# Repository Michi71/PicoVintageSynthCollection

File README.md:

# PicoVintageSynthCollection

Thirteen vintage synthesizer emulations for the RP2350, built from one shared
codebase. Same board, same core, one firmware image per instrument.

<p align="center">
  
  <br>
  
  <br>
  <sub>Rendered on a host from the firmware's own drawing code
  (<a href="tools/host_tests/ui/README.md">tools/host_tests/ui</a>) &mdash; what the OLED shows, pixel for pixel.</sub>
</p>

## Demo

<p align="center">
  
  <br>
  <a href="https://youtu.be/6L494ZGSKgw">&#9654; PicoFaceM1 demo on YouTube</a> &mdash; the Korg M1 on the project's own PCB
  <br><br>
  <a href="https://youtu.be/cG6gyhaqCxE">&#9654; Earlier demo of the collection</a>
</p>

## Project philosophy and architecture

**Translation, not emulation.** No instrument here runs an emulated CPU or
system bus, as MAME-style emulators do. Each one is a native C++17 engine on a
shared core, and how it was derived depends on what the original leaves to
work with:

- The **Korg M1** and the **Roland D-50** come from a disassembly of the
  original operating system: envelopes, filters, voice allocation and the
  effect algorithms were read out of the firmware and rewritten as native
  code that plays the machine's own PCM data. Where firmware, plugin and ear
  disagree, the firmware wins.
- The **Roland CM-32L** is the one that runs somebody else's engine: the
  synthesis core of [munt](https://github.com/munt/munt)'s mt32emu, which
  models the LA32 chip and restates the module's firmware, with the original
  control and PCM ROM. It was reshaped to fit the board - both cores render,
  the code that plays runs from RAM - and still produces upstream's samples.
- The **JV-880** and the **RD/MKS-20** are written over the original PCM data
  and calibrated against a reference emulator of the original firmware, which
  runs on the host only and is not part of this repository.
- The analog and modern instruments are modeled from manuals, schematics and
  published work; the License section lists every upstream.

**Lean because it has to be.** Every engine has to finish its audio blocks on
an RP2350, a microcontroller with 520 KB of RAM, overclocked to 444 MHz. That
budget leaves no room for waste: tables live in flash, the voice loops are
measured on the device, and an instrument that does not fit does not ship.
The same engine sources also build unchanged on macOS for the host tests,
which is what makes them portable to other targets.

**Made for reuse.** The engines are separate from the core that drives the
hardware (display, encoders, MIDI, audio output). Taking an engine, a filter
or an effect into your own hardware, plugin or application is an explicit
goal, under the GPL-3 terms below.

**How it is made.** The project is developed with an AI coding agent
(Claude Code); the rules it works under are in [CLAUDE.md](CLAUDE.md). It
does not build itself. The author sets the goals, the order of authority and
the bar for "done", decides every trade-off, builds the hardware and tests
on it: no firmware change is merged without a hardware test. The agent does a large
share of the disassembly analysis and the code. Every result is checked
against the original firmware, a reference render or a measurement before it
lands, and what could not be verified is written down as such in the
instrument's documentation.

## Instruments

| Folder | Instrument | Binary |
|---|---|---|
| [instruments/PicoFaceYC](instruments/PicoFaceYC/README.md) | Yamaha reface YC (drawbar organ) | PicoFaceYC.uf2 |
| [instruments/PicoFaceCP](instruments/PicoFaceCP/README.md) | Yamaha reface CP (electric piano, mdaEPiano) | PicoFaceCP.uf2 |
| [instruments/PicoFaceDX](instruments/PicoFaceDX/README.md) | Yamaha reface DX (4-operator FM) | PicoFaceDX.uf2 |
| [instruments/PicoFaceJ6](instruments/PicoFaceJ6/README.md) | Roland Juno-6 | PicoFaceJ6.uf2 |
| [instruments/PicoFaceMD](instruments/PicoFaceMD/README.md) | Minimoog Model D | PicoFaceMD.uf2 |
| [instruments/PicoFaceSM](instruments/PicoFaceSM/README.md) | ARP/Eminent Solina String Ensemble | PicoFaceSM.uf2 |
| [instruments/PicoFaceOB](instruments/PicoFaceOB/README.md) | Oberheim OB-X (engine ported from OB-Xf) | PicoFaceOB.uf2 |
| [instruments/PicoFaceVS](instruments/PicoFaceVS/README.md) | Sequential Prophet VS (native vector-synthesis engine, with edit pages and SysEx) | PicoFaceVS.uf2 |
| [instruments/PicoFaceRD](instruments/PicoFaceRD/README.md) | Roland RD / MKS-20 (sample piano) | local build only |
| [instruments/PicoFaceJV](instruments/PicoFaceJV/README.md) | Roland JV-880 (native engine over the original PCM data) | local build only |
| [instruments/PicoFaceD5](instruments/PicoFaceD5/README.md) | Roland D-50 (native LA engine over the original PCM data) | local build only |
| [instruments/PicoFaceM1](instruments/PicoFaceM1/README.md) | Korg M1 (native engine over the original PCM data, with edit pages and SysEx) | local build only |
| [instruments/PicoFaceCM](instruments/PicoFaceCM/README.md) | Roland CM-32L (mt32emu's LA synthesis core over the original ROMs, eight parts and rhythm, on both cores) | local build only |

The RD, the JV-880, the D-50, the M1 and the CM-32L are the exceptions to "download and flash":
they only build where the respective ROM set is present, and those ROMs are not
distributable, so none of them is in the release binaries. Without them
the configure step skips them and the eight above are unaffected. All of them run
on the hardware; see the flash note below for the one build option the JV-880
needs on a small board.

## Hardware

- RP2350; the reference board carries 16 MB of flash, 4 MB is enough for every
  instrument but the JV-880 (see [How much flash an instrument needs](#how-much-flash-an-instrument-needs)).
  **The board must feed the core from the RP2350's own regulator** -- see
  *The board has to take the overclock* below before buying anything cheap.
- I2S audio (PCM5102 DAC)
- 128x64 OLED over I2C (SH1106)
- Three rotary encoders with push buttons
- USB MIDI and DIN MIDI

The pin map is the same for every instrument and lives in
[core/include/project_config.h](core/include/project_config.h).

**Which RP2350 board.** The default build assumes a Pico-2-format board with an
RP2350**A** -- Pico 2, Waveshare RP2350-Plus and the like -- where I2S sits on
GP26/27/28 at header pins 31/32/34. The Waveshare **RP2350B-Plus-W** has the
same header but carries **GP40/41/42** at those three positions (the RP2350B's
ADC0-2 take the Pico's ADC spots; GP26-28 are only on the pads underneath), so
a default image on it drives the I2S lines into thin air: display, MIDI and
encoders work, only the sound is missing, and every counter reads healthy. It
is a build-time choice, not a wiring one -- see *Building* for
`-DPICOFACE_BOARD=rp2350b_plus_w`.

**The board has to take the overclock.** These engines are budgeted for a
core clock of **444 MHz** (480 for the RD) at a core voltage of **1.60 V**:
three times the RP2350's rated 150 MHz, and a voltage above what the SDK
allows without an explicit override. That is not a tuning option, it is the
design point -- below it the instruments do not finish their audio blocks.
The firmware sets that voltage through the chip's on-board regulator, so the
board has to route the core supply (`DVDD`) through that regulator, the way
the Pico 2 reference design does. **Known good:** Raspberry Pi Pico 2,
Waveshare RP2350-Plus, Waveshare RP2350B-Plus-W (with its build variant).
**Known bad:** unbranded 16 MB "RP2350" boards from marketplace sellers. One
was bought to settle issue #107: its chip and flash are fine, but the
regulator register has no effect on its core voltage, so the core stays at the
board's fixed supply and stops dead at 312 MHz. No build option, flash timing
or stepping has anything to do with it, and no firmware can get 444 MHz from
such a board. The symptom is either nothing on the screen with the release
image, or "boots at 300 MHz, no sound" with a downclocked build. If a board
does neither of the things above, the working image is the diagnosis: build
`PicoFaceMD` with `-DPICOFACE_BOOT_DIAG=ON` and read the last line on the
screen; the whole investigation, with the images that separate flash, core
and voltage, is in the MD README under
[The board that stops at 300 MHz](instruments/PicoFaceMD/README.md#the-board-that-stops-at-300-mhz-a-core-voltage-the-register-cannot-reach).
Please check that section before opening an issue about a board that will
not start: a chip marked `A4` is not the reason either (the splash shows the
bootrom revision as `b4` now, and it changes nothing).

**If the screen stays dark.** The panel is on I2C at 1 MHz with only the chip's
internal pull-ups. That is above what an SH1106 datasheet promises (400 kHz) and
it is what the reference board runs, because the display push is paced in half
tile rows of roughly 1.5 ms of I2C each -- the bus rate is directly the UI's
frame time, and 400 kHz would make a full screen 60 ms instead of 24. On longer
jumper leads it is the first thing to suspect. Build with
`-DPICOFACE_OLED_I2C_HZ=400000`, and consider real 2.2k-4.7k pull-ups before
blaming the display.

A display that is simply absent costs nothing: the I2C write returns an error on
a NACK and the firmware carries on. A display that *holds a line low* used to
take the whole instrument down -- the wait for the bus is unbounded, and the
first transfer happens before the splash loop, which is the only place USB gets
serviced during startup, so the board would not even enumerate. It reads exactly
like a firmware that does not boot. That write is now bounded at 5 ms and the
panel is written off after twenty consecutive failures, so a broken display
costs you the display and not the MIDI, the audio and the encoders.

**On the board setting.** The build defaults to `PICO_BOARD=sparkfun_promicro_rp2350`,
and that is a statement about flash size rather than about hardware: the
prototype runs a Waveshare RP2350-Plus, and the SparkFun definition was picked
because it declares 16 MB where the plain `pico2` definition declares 4. Any
RP2350 board with 16 MB works if the pins above are reachable on it. For a
Pico-format board the honest pair is

```bash
cmake -S . -B build -G Ninja -DCMAKE_BUILD_TYPE=Release -DPICO_BOARD=pico2 -DPICO_FLASH_SIZE_BYTES=16777216
```

Without that second flag, `pico2` caps the image at 4 MB. The CP's sample
sets were cut for exactly that size, so every instrument but the JV fits
within it (the CP at 3.99 MB, with 190 KB to spare); the flag is for the JV,
and for a board that really has 16 MB. Nothing else in the SparkFun definition
reaches the firmware: the flash timing and the system clock are set by the project itself in
[core/src/pico_hw.cpp](core/src/pico_hw.cpp), and `PICO_FLASH_SPI_CLKDIV` is
identical in both. The one thing it declares that the prototype does not have is
an 8 MB PSRAM region on GPIO 19 — nothing is placed there, so it costs nothing,
but PSRAM is not a thing to reach for on this hardware without checking the
board first.

### Switching instruments

One board, thirteen firmware images, so choosing a different instrument is something
you do rather than something a factory does once. **Hold all three encoder
buttons together.** After half a second the display takes over and counts down
from two; let go and nothing happens. Hold it out and the board silences itself,
drains the audio it had already queued, and reappears as the `RPI-RP2` drive —
drop the next `.uf2` on it.

No button combination in any instrument uses all three at once, so it cannot
happen by accident, and the BOOTSEL button on the module is never needed for
this. Keep that button reachable anyway: if a firmware is too broken to reach
its own user interface, BOOTSEL plus a power cycle is the way back.

### How much flash an instrument needs

The reference board carries 16 MB. That is not a requirement of the design:
three instruments ship sample data, and only one of them needs a build option
to fit the 4 MB that a base Raspberry Pi Pico 2 and many other RP2350 boards
provide:

| Instrument | Image | On a 4 MB board |
|---|---|---|
| YC, DX, J6, MD, SM, OB | 90-190 KB | fits anywhere |
| PicoFaceVS | 0.4-0.6 MB | fits anywhere |
| PicoFaceCP | 3.99 MB | fits, 190 KB to spare |
| PicoFaceJV | 4.34 MB | only with `-DPICOFACEJV_4MB=ON` (3.76 MB, banks A+B) |
| PicoFaceD5 | 0.86 MB | fits |
| PicoFaceCM | 1.28 MB | fits |
| PicoFaceM1 | 4.48 MB | no (4 MB of PCM; no reduced build) |
| PicoFaceRD | 2.56 MB | fits |

The JV's reduced variant drops something real: the user bank, and the 22
samples only those patches used. Banks A and B are otherwise untouched --
nothing is resampled or requantised.

**The RD used to need one too, and no longer does.** Its packs held four
sampled velocity layers of every note; they hold the parameter ROM's own
corners now and the engine interpolates, which is both exact at all 128
velocities and a fifth the size. The whole instrument went from 5.15 MB to
2.56 MB. `-DPICOFACERD_MODEL=MKS20` or `=MK80` still builds one machine on its
own -- eight patches, and half a ROM set is enough for it -- but nobody needs
it to fit a board any more.

**The CP has no reduced variant either, and needs none.** It used to be
4.22 MB and carried its five built sample sets as one indivisible whole, with
no subset to drop; the sets were then cut for a 4 MB flash without dropping
anything: every sample keeps its attack byte for byte and loops 40-100 ms
earlier, at a loop cycle chosen to stay within 1 dB and 10 % spectral centroid
of the cycle it looped before. The rule and the numbers are in
[tools/cp_sampleprep](tools/cp_sampleprep/README.md#fitting-a-4-mb-flash).
Anything from 8 MB up holds any of the thirteen instruments. The D-50 is the one
sample-based instrument that never needed cutting -- its whole sample ROM is
512 KB.

An oversized `.uf2` fails to copy in a way that names no reason: the file
transfer stops or the drive rejects it, with nothing on screen about flash size.
That is the symptom, and it is not a corrupt download.

## Building

```bash
git clone --recurse-submodules https://github.com/Michi71/PicoVintageSynthCollection.git
cd PicoVintageSynthCollection
cmake -S . -B build -G Ninja -DCMAKE_BUILD_TYPE=Release
cmake --build build
```

The artifacts are then in `build/<instrument>.uf2`.

**Board variant.** `-DPICOFACE_BOARD=pico` (the default) builds for any
Pico-2-format RP2350A board. `-DPICOFACE_BOARD=rp2350b_plus_w` builds for the
Waveshare RP2350B-Plus-W: it selects an RP2350B board profile (48 GPIOs, 16 MB),
puts I2S on GP40/41/42, and re-bases PIO0 to GPIO 16-47 before the I2S program
is loaded, because an RP2350 PIO addresses either GPIO 0-31 or 16-47. The firmware
also puts such a board's flash into quad by itself when the bootrom left it in
dual -- the Puya P25Q128H on the reference board ships with its quad-enable bit
clear, and the bootrom never sets one -- and then tops the flash timing ladder
one rung lower (111 MHz instead of 148; RD 96 instead of 120): that part
verifies 111 MHz in quad and hangs at 148, and a rung that hangs cannot be
stepped down from. See the PicoFaceMD README, *The bit the bootrom never sets*. A board
with a faster flash can ask for the full rung with
`-DPICOFACE_QMI_M0_TIMING_TARGET=PICOFACE_QMI_M0_TIMING_RX4`. The released UF2s
are the default variant; the RP2350B build is one cmake flag away and produces
the same thirteen images.

```bash
cmake -S . -B build-b -G Ninja -DCMAKE_BUILD_TYPE=Release -DPICOFACE_BOARD=rp2350b_plus_w
cmake --build build-b
```

**The splash screen names the build.** Every instrument shows a version taken
from `git describe`, not a number typed into its `instrument.cmake`: on a
release tag it is the release (`1.7.0`), anywhere else it says how far past that
tag and from which commit (`1.7.0-4-ga39504b`), and a trailing `+` means the
tree had uncommitted changes when it was built. The About page shows the same
string. Quote it in a bug report and the image is identified exactly; the
version used to read `0.1` in every build ever made, which identified nothing.

A tarball without `.git` builds fine and shows `unknown`.

### The five that need ROMs

`PicoFaceRD`, `PicoFaceJV`, `PicoFaceD5`, `PicoFaceM1` and `PicoFaceCM` play the original machines' own
data, which is not distributable. Each looks in its own `roms/` directory —
`instruments/<name>/roms/`, gitignored — and removes itself from the build with
a note if what it needs is not there. Nothing else is affected.

| | what goes in `roms/` | |
|---|---|---|
| **PicoFaceCM** | the CM-32L's control ROM v1.02 (64 KB) and PCM ROM (1 MB) | identified by SHA-1, so **names do not matter** |
| **PicoFaceD5** | two PCM ROMs and a program EPROM | identified by CRC32, so **names do not matter** |
| | | plus optional `*.syx` bulk dumps for the patch banks |
| **PicoFaceJV** | `jv880_rom2.bin`, `jv880_waverom1.bin`, `jv880_waverom2.bin` | exact names, 256 KB + 2 MB + 2 MB |
| **PicoFaceM1** | `IC36.bin` … `IC43.bin`, `IC30.bin`, the two halves of the original OS (Rev 19), the factory preload `M1preld.syx` | PCM by name; OS halves and dump by content |
| **PicoFaceRD** | `mks20_15179736.BIN` … `41.BIN`, `MK80_IC5.bin`, `MK80_IC6.bin`, `MK80_IC7.bin` | exact names, 128 KB each |
| | `pack_p0.rdp` … `pack_p15.rdp` | **built, not found** — see below |

**The RD needs one thing nobody else does.** Its sixteen `.rdp` packs are note
descriptors derived from those ROMs, and they have to be made once:

```bash
R=instruments/PicoFaceRD/roms
python3 tools/rd_extract/rd_descramble.py $R \
    RD200_B.bin mks20_15179757.BIN /tmp/prog.bin /tmp/prm.bin
python3 tools/rd_extract/rd_make_packs.py /tmp/prog.bin /tmp/prm.bin $R \
    0 0x000000 1 0x008000 …
```

Python and the ROMs, nothing else -- no emulator, no toolchain beyond the one
already building the firmware.

**To check that all of this actually works from scratch**, `tools/check_clean_build.sh`
clones into a temporary directory, copies the ROMs in from outside git, and
builds all thirteen. That last part is the point: the ROM sets are not in this
repository and must never be, so a build here is the one thing CI cannot cover.
Name a directory to build there instead and keep the result; add `--variants`
for the reduced images too.

RD also builds as a single machine — `-DPICOFACERD_MODEL=MKS20` (1.73 MB) or
`=MK80` (1.23 MB), eight patches each, and only that machine's ROMs are needed.
The default is both machines and 2.56 MB, which fits a 4 MB board. See
[`instruments/PicoFaceRD/README.md`](instruments/PicoFaceRD/README.md) for the
whole recipe and all sixteen patch offsets.

Building a single instrument:

```bash
cmake -S . -B build -G Ninja -DCMAKE_BUILD_TYPE=Release -DPICOFACE_INSTRUMENTS_FILTER=PicoFaceMD
cmake --build build
```

### If the very first cmake call dies with an architecture error

On macOS a mixed package manager prefix produces this, and it reads like a
problem with the project:

```
dyld: Library not loaded: /opt/local/lib/libarchive.13.dylib
  Referenced from: /opt/local/bin/cmake
  Reason: (mach-o file, but is an incompatible architecture (have 'arm64', need 'x86_64'))
Abort trap: 6
```

It is not. The complaint comes from `dyld` about loading `cmake` itself, before
any of this repository is read, and "need 'x86_64'" means the `cmake` binary is
an Intel build sitting next to Apple Silicon libraries — a MacPorts or Homebrew
prefix that was installed under Rosetta, or carried over from an Intel Mac
without the migration. Check with:

```bash
uname -m                 # arm64 on Apple Silicon
file $(which cmake)      # must say the same
```

If they disagree, reinstall the toolchain for the machine's own architecture
(MacPorts documents a migration procedure for exactly this). Apple Silicon
itself is fine: the collection is developed on it.

## Repository layout

```text
core/            shared runtime: audio pipeline, hardware, USB/DIN MIDI, GUI, persistence
cmake/           picoface_add_instrument() and the SDK import helpers
lib/             third-party static libraries (audio, encoder, u8g2) and the SDK submodules
instruments/     one folder per instrument: instrument.cmake, src/, include/, doc/, README.md
tools/           host-side tools; not part of any firmware image
docs/            documentation shared by all instruments
hardware/        the module as a board: schematic, two layouts, panel, parts, and
                 what the first built pair taught
img/             the instruments' screens and the panel sheets above, rendered
                 from the firmware by tools/host_tests/ui
```

## Documentation

Shared:

- [Architecture](docs/ARCHITECTURE.md) - how core and instruments fit together, and why
- [Adding an instrument](docs/ADDING_AN_INSTRUMENT.md) - the three steps needed
- [The module bus](docs/MODULE_BUS.md) - the hardware interface several modules in one
  case would share: power, MIDI and audio. Planned, not built
- [Hardware](hardware/README.md) - the module as a 10 HP Eurorack board: schematic,
  the two layouts and the panel, parts, and the first built pair
- [Host tools](tools/README.md)

Per instrument, under `instruments/<name>/doc/`: MIDI implementation charts,
persistence formats, preset tables and the engineering logs of the individual
ports. The per-instrument README links them.

Manufacturer manuals and service documentation are **not** part of this
repository. Where an emulation follows a specific manual or schematic, the
instrument's README names the document so it can be obtained separately.

## Status

**All thirteen instruments build from a single configure run, each with its own
USB PID, and all thirteen run on the hardware.**
Eight are in the release binaries; the RD, the JV-880, the D-50, the M1 and the CM-32L need a
local ROM set and are therefore built locally only.
Open points are listed in [docs/ARCHITECTURE.md](docs/ARCHITECTURE.md),
section 8.

[Progress data](decomphub.progress.json) - the same figures in machine-readable
form, scoped per measurement, for project directories such as DecompHub.

## License

**GNU General Public License, version 3 or later** - see [LICENSE](LICENSE).
Copyright (C) 2026 Michi71.

The collection was assembled in August 2026 from seven single-instrument
repositories -- YC, CP, DX, RD, J6, MD and SM; OB, JV, D5, M1, VS and CM were added
here afterwards, which is why the number is seven and not thirteen. Each of those seven
already shipped the identical GPL-3 licence text, and every instrument README
states GPL-3. It is also the lowest common denominator of what the engines are
built on. Where an instrument derives from someone else's work:

| Part | Upstream it derives from | That upstream's license |
|---|---|---|
| core, cmake, tools | own work | - |
| PicoFaceYC | [OpenB3 / BeatrixCPP](https://github.com/pantherb/setBfree) - tone generation *concepts* only, no code | AGPL-3.0 upstream, does not reach here; see below |
| PicoFaceCP | [mda-EPiano](https://sourceforge.net/projects/mda-vst/) (engine, in tree) | GPL-3.0-or-later |
| PicoFaceDX | an ESP32 reface DX emulation (engine) | see that project |
| PicoFaceRD | [giulioz/rdpiano](https://github.com/giulioz/rdpiano) + MAME (reference emulator; host-side only, not in this repository) | GPL |
| PicoFaceJ6 | [junox](https://github.com/dzannotti/junox) (patch table, parameter scaling) | GPL-3 |
| PicoFaceMD | [BelaMiniMoogEmulation](https://github.com/lbros96/BelaMiniMoogEmulation) (ladder filter) | stated by its author to be under no copyright |
| PicoFaceSM | [string-machine](https://github.com/jpcima/string-machine) (DSP models) | Boost Software License 1.0 |
| PicoFaceOB | [OB-Xf](https://github.com/surge-synthesizer/OB-Xf) (engine) | GPL-3.0-or-later |
| PicoFaceJV | own engine over the machine's own PCM data, measured against [giulioz/jv880_juce](https://github.com/giulioz/jv880_juce) (host-side reference; tone field layout) | non-commercial; not vendored, see below |
| PicoFaceM1 | own engine over the machine's own PCM and tables, from a disassembly of the M1 OS; no third-party code | - |
| PicoFaceVS | own engine, from a disassembly of the Prophet VS OS, its service manual and the CEM3379 data sheet; no third-party code. The waves are recomputed from a harmonic table derived from the original's | - |
| PicoFaceCM | [munt](https://github.com/munt/munt)'s mt32emu 2.8.6 (engine): a modified copy in `instruments/PicoFaceCM/mt32emu`, with its licence text and a list of every change | LGPL-2.1-or-later |
| PicoFaceD5 | [munt](https://github.com/munt/munt) - the LA32's wave generation and the Boss reverb topology as that project *documents* them, no code | LGPL-2.1-or-later upstream, does not reach here; see below |

Two rows in that table need a sentence more than a table cell holds.

**PicoFaceRD** used to carry the reference emulator's sources in the tree, and
three decoded ROM sets with them. Neither is here any more. The emulator is a
separate checkout the regression harness is pointed at, and the sample data is
built at configure time from a local ROM set into a blob -- the same arrangement
as the JV and the D5, and for the same reason. What the device plays is
`RdNewEngine` over descriptors that emulator captured offline.

**PicoFaceJV** contains none of that emulator's code, and cannot: its licence
forbids commercial use and fits neither MIT nor GPL-3. It was used as a host-side
measuring instrument — the harness in `tools/jv_extract/` drives it to take the
readings the engine was calibrated against, and the patch and tone field layout
comes from its `dataStructures.h`. The engine itself is written from the ROM
formats. `tools/jv_extract/README.md` records the reasoning; the work is Giulio
Zausa's, and his emulator in turn derives from [NukeYKT's
Nuked-SC55](https://github.com/nukeykt/Nuked-SC55).

`instruments/PicoFaceOB/` additionally carries its own `LICENSE`, identical in
text, because that instrument's engine is a direct port of OB-Xf and its files
keep the upstream copyright headers. Every instrument builds into its own
binary, so a stricter licence on one of them stays confined to that binary.

Source files carry a two-line SPDX header rather than the full notice, to keep
it out of the way of the code. Three kinds exist:

- own work: `GPL-3.0-or-later` plus the copyright line;
- ported trees (`instruments/PicoFaceDX/include/dx_engine/`): the licence line
  plus a note that copyright is shared with the upstream authors - no sole
  claim is made there;
- upstream files (`instruments/PicoFaceOB/include/obxf/`, CP's `mdaEPiano.*`,
  the SDK-derived `usb_descriptors.c`,
  `get_serial.*` and `tusb_config.h`): untouched, they keep the header they
  came with. The last four are MIT and BSD-3-Clause, not GPL.

**On PicoFaceD5 and munt.** The D-50 and the MT-32 share the LA32 sound chip,
and the MT-32 emulator [munt](https://github.com/munt/munt) has read that chip
out and written down what it does: how a cutoff becomes the width of a cosine
edge, how the resonance decays, and - from the same era's Boss reverb chip,
whose data lines were traced by Lord_Nightmare, balrog and Mok - the topology
the reverb here follows. munt is LGPL-2.1-or-later. Nothing was copied: the
engine under `instruments/PicoFaceD5/include/d5_engine/` was written for this
project from that written description and from the D-50's own firmware, which
is why no file there carries an upstream copyright header. The description is
what mattered, and a description is not the program.

**On PicoFaceYC and the AGPL.** OpenB3 / BeatrixCPP, whose tone generation
concepts the YC drawbar engine follows, is AGPL-3.0 - stricter than GPL-3, and
not something that can be dropped by relicensing. It does not apply here: the
engine under `instruments/PicoFaceYC/include/yc_engine/` was written for this
project and contains no upstream code, which is why no file there carries an
upstream copyright header. Copyright covers the expression, not the concepts,
so GPL-3 is the right licence for it.

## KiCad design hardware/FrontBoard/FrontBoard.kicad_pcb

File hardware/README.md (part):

# Hardware

The module this firmware has been running on, turned into something
reproducible: the dimensions and decisions the board was drawn to, worked out
against the parts actually in hand and written down before the layout rather
than after. The first pair of boards has been fabricated, assembled and is
running the firmware since September 2026 - it is the reference hardware now,
see [The first built pair](#the-first-built-pair) for what powering it up
taught.

The schematic is drawn: the KiCad 10 project in
[PicoVintageSynthCollection/](PicoVintageSynthCollection/) (root sheet plus
`main_board`, `front_board`, `panel`; ERC clean), with a PDF export next to it
([PicoFace-schematic.pdf](PicoVintageSynthCollection/PicoFace-schematic.pdf)).

**Both boards are laid out**: [MainBoard/](MainBoard/) and
[FrontBoard/](FrontBoard/), routed, DRC clean; and the panel is a board in its
own right in [Panel/](Panel/). Both boards have been made from these files.

The interface *between* several modules — power, MIDI, audio — is a separate
document: [The module bus](../docs/MODULE_BUS.md).

## Format

3U Eurorack, 10 HP. The panel is 50.8 x 128.5 mm and 1.6 mm thick, which is
mechanical rather than cosmetic: the EC11 encoders have a 5 mm threaded bushing,
and 1.6 mm of panel leaves 3.4 mm for the nut. A 2 mm panel leaves 3.0 mm, which
works but has no margin.

**Cut it to 50.4 mm, not 50.8.** 10 HP is 10 x 5.08 mm, and that nominal figure
is the space the module occupies in the rack, not the width of the metal. A panel
made to it has no room for the tolerances of its own edge, of its neighbours, or
of the rails, and a full row will bind rather than sit flat. Roughly 0.4 mm under
is the usual allowance. The height is not affected: 128.5 mm is already the
Eurorack panel height, 3U less the clearance the rails need.

The layout is [Panel/panel_10hp.svg](Panel/panel_10hp.svg) (CorelDRAW source
next to it), measured against the real parts: the display on top, the SELECT
encoder between the RUN and BOOT buttons, PARAM A and B in a second row, the
four jacks along the bottom below the board. 14 HP was the plan as long as the
three encoders had to share one row; with SELECT in its own row and the jacks
off the board, 10 HP closes.

## The governing dimension

**The board sits 6.5 mm behind the panel.** That is the EC11's body height and
nothing else negotiates with it — every other panel-facing part has to reach the
same plane:

- the **display** module is 2.8 mm thick, so it rides on 3.5 mm standoffs
- the **jacks** could not reach it at all, which is why they are panel-mounted
  and wired (see below)

## Drill and cutout list

Origin top left, X right, Y down, panel 50.8 x 128.5 mm. Numbers read off
`panel_10hp.svg` (1 unit = 0.01 mm there); the SVG carries a 50 mm calibration
bar.

| Element | X | Y | Machining |
|---|---|---|---|
| Mounting M3 | 7.5 / 43.3 | 3.0 | 3.2 dia |
| Mounting M3 | 7.5 / 43.3 | 125.5 | 3.2 dia |
| Display window | 25.4 | 30.0 | 30 x 16 (X 10.4–40.4, Y 22–38) |
| Encoder SEL | 25.4 | 60.58 | 7.0 dia, 15 mm knob |
| RUN | 10.0 | 60.58 | 4.0 dia for the 6x6 tact switch actuator |
| BOOT | 40.8 | 60.58 | 4.0 dia for the 6x6 tact switch actuator |
| Encoder A | 12.9 | 85.61 | 7.0 dia, 15 mm knob |
| Encoder B | 37.9 | 85.61 | 7.0 dia, 15 mm knob |
| MIDI in | 8.15 | 109.6 | 8.2 dia (M8 thread), 10 mm body |
| MIDI out | 19.65 | 109.6 | 8.2 dia (M8 thread), 10 mm body |
| Out L | 31.15 | 109.6 | 8.2 dia (M8 thread), 10 mm body |
| Out R | 42.65 | 109.6 | 8.2 dia (M8 thread), 10 mm body |

No USB cutout: the 10 HP panel has no room for a USB lead, so USB stays at
the module's own socket.

The display module is **35.4 x 33.5 mm** with its four M2 holes **30.4 x 28.5**
apart, set 2.5 mm in from its top-left corner — all four numbers off the part
itself. Centred on the board it sits at X 7.7–43.1, Y 15.0–48.5, which puts the
holes at X 10.2 / 40.6 and Y 17.5 / 46.0. The two boards, 45 x 80 mm each, sit
at X 2.9–47.9, Y 14.0–94.0 behind it; the jack row is below the boards.

**The display's pin order is not the common one.** Measured on the part in hand:
**1 VDD, 2 GND, 3 SCK, 4 SDA**, numbered from the display side with pin 1 on the
left. The order most modules use — GND, VCC, SCL, SDA — would have put 3.3 V on
this module's ground pin and killed it on first power-up. The header is centred
on the module's top edge, which is where DS1 sits.

**The window is cut to the pixels, not to the glass.** On the 1.3 inch module the
active area starts 7.35 mm below the module's top edge and is 14.7 mm tall, so
its centre lands 14.7 mm below that edge — the glass around it is 19 mm tall and
sits differently. Cutting to the glass would leave an uneven border.

Clearances, so the numbers can be checked rather than trusted: the display
glass ends at Y 48.5 and the SELECT knob begins at 53.1; the 15 mm knob leaves
4.9 mm to each 6 mm button; the PARAM knobs (78.1–93.1) end 0.9 mm above the
board edge at Y 94 and stand 10 mm apart; the jack bodies (10 mm) sit 1.5 mm
apart at 11.5 mm pitch — fine for round nuts, an 11 mm hex nut is marginal.

## The panel as a board

The drawing is not a manufacturable file. `panel_10hp.svg` says where the holes
go and can be read by a person or a laser cutter; a board house needs the
outline on a copper-stackup layer and every opening as a closed contour. So the
panel is drawn a second time, as [Panel/Panel.kicad_pcb](Panel/Panel.kicad_pcb)
— a two-layer board 1.6 mm thick with **no copper on it at all**, which is the
usual way to have a fab cut a front panel: same process, same price bracket, and
the silkscreen comes with it instead of needing a separate print.

**The coordinates are the table above shifted 0.2 mm left.** The table is drawn
on the 50.8 mm nominal; cutting to 50.4 takes 0.2 mm off each edge, and
everything has to follow or the pattern sits off-centre. It stays symmetric
after the shift, which is the check: SELECT lands on 25.2, exactly half of 50.4,
and each pair still mirrors (mounting 7.3 / 43.1, buttons 9.8 / 40.6, PARAM 12.7
/ 37.7, jacks 7.95 / 42.45). The mounting holes end up ±17.9 mm from the panel
centre, which is where the rail thread expects them.

**What is drilled and what is routed** is decided by one number: 6.3 mm, the
largest drill most fabs keep.

| Opening | Layer | Why |
|---|---|---|
| outline 50.4 x 128.5 | `Edge.Cuts` | |
| display window 30 x 16 | `Edge.Cuts` | rectangular |
| 3 x encoder 7.0 dia | `Edge.Cuts` | over 6.3 |
| 4 x jack 8.2 dia | `Edge.Cuts` | over 6.3 |
| 4 x mounting 3.2 dia | NPTH | |
| 2 x button 4.0 dia | NPTH | |

Routed circles are cut with an end mill and come out a little rougher than a
drilled hole, which is of no consequence behind a nut. The display window's
inside corners will carry the mill's radius, about 1 mm — that is normal and the
module's bezel covers it.

**Every label sits above what it names**, including the jack row. That is not
symmetry for its own sake: a patch cable hangs down out of a Eurorack jack and
covers whatever is printed below it, so the first drawing — labels under the
jacks, in the space that looked free — would have been legible only on an
unpatched module. Checked rather than eyeballed: no silkscreen stroke falls
within 0.3 mm of any opening or the board edge, and none of it disappears under
a 15 mm knob or an 11 mm jack nut.

**The top side is the front.** Decided, and the board file is drawn to it: the
legend sits on `F.SilkS` unmirrored, so the side the fab prints as top is the
side that faces the player. Say it in the order anyway — a panel has no
components to make the intent obvious, and a fab that guesses has a fifty-fifty
chance of printing the legend on the inside. White on black is the usual choice.

DRC reports six warnings and nothing else: the six hole footprints are generated
in the board file rather than pulled from a library, so the library-parity check
has nothing to compare them against. Same class of warning the other two boards
carry, and it does not reach the Gerbers.

## Two boards

Both boards are **45 x 80 mm, two layers**.

*Renders under [render/](render/); how they are made and what they settled is in
[3D view](#3d-view) below. The encoders and the display are stand-in models, and
the module is drawn as a Pico.*

**Front board**, 6.5 mm behind the panel, carries everything the format dictates
— and that 6.5 mm is a hard ceiling for anything on its panel side, which is why
the jack wires are soldered into J8 rather than plugged into a header: a 2.54 mm
header stands 8.5 mm tall and would hit the panel. It carries:
three EC11 encoders, the RUN and BOOT tact switches (6x6, four pins; the
actuator has to reach through 6.5 mm of gap plus the 1.6 mm panel, so the 9.5
mm or taller types), the display on standoffs, the encoder pull-ups, and the
header J8 for the panel-wired jacks.

**Main board** behind it carries what does not care about the format: the
module on sockets, the PCM5102, the MIDI circuitry, and the bus connectors.

They join with **two 1x12 headers** (J1/J2 male on the main board, J3/J4
sockets on the front board) — two rather than one because they also hold the
boards parallel. Nineteen signals: I2C 2, encoders 9, MIDI 4, audio 2, RUN,
BOOT; plus 3V3, VSYS and three GND = 24. MIDI is four lines rather than two
because the current loop crosses the headers — the opto-coupler and its
resistors stay on the main board, where the bus MIDI RX joins the same node —
and the two extra grounds are what makes a single 24-way link acceptable for
audio. The plan said "roughly nineteen" and two 10-pin strips; the schematic is
where the count became exact.

The split is the point. A different enclosure means a new front board; the main
board does not change.

## Why the jacks are wired rather than soldered to the board

The available jack has its collar 2.9 mm above the board and its thread ends at
8.9 mm. With a 1.6 mm panel and a 2 mm nut, the panel can sit no further out
than 5.3 mm — and the encoders put it at 6.5 mm. Short by 1.2 mm, with no slack
anywhere to take it out of.

So the jacks mount to the panel and wire back to a 10-pin header (J8). That
removes the constraint instead of working around it: the board stops having an
opinion about which jack fits, which is what makes the three-conductor MIDI
sockets possible at all — those need TRS. The jacks are the M8-thread panel
type (10 mm body, nut, solder lugs), stereo for MIDI, mono or stereo for audio;
with a stereo jack on an audio output the ring is simply left open. On a metal
panel the bushing ties the sleeve to the panel — fine for the three grounded
jacks, and for MIDI IN either an insulating washer or accepting it (the opto
still isolates the loop).

## Parts

Already in hand: Waveshare RP2350-Plus (16 MB), three EC11 with 5 mm bushings, 15 mm
knobs, PCM5102 module.

Still needed:

| Part | Qty | Note |
|---|---|---|
| OLED 1.3" SH1106, I2C, 4-pin | 1 | 35.4 x 33.5 mm |
| 3.5 mm jack, panel mount, M8 thread, 10 mm, solder lugs | 4 | 2× stereo (MIDI), 2× mono or stereo (audio) |
| Tact switch 6x6, 4-pin, actuator ≥ 9.5 mm | 2 | RUN, BOOT — on the front board |
| Header strips 12-pin, male + female | 2 each | board to board (J1/J2, J3/J4) |
| Header strip 10-pin | 1 | panel jacks (J8) |
| Socket strips for the module | 2 | keep the module replaceable |
| Socket strips 1x6 and 1x9 | 1 each | the PCM5102 module, likewise replaceable |
| H11L1 optocoupler (+ DIP-6 socket) | 1 | MIDI in, Schmitt trigger type |
| 220R, 4k7, 1N4148, 100 nF | 1 each | MIDI in (4k7 pull-up on the H11L1, 100 nF bypass) |
| 33R, 0.5 W | 2 | MIDI out at 3.3 V (the source resistor sees a pin-4 short) |
| 1N5817 Schottky | 1 | bus 5 V into VSYS |
| BAT85 Schottky | 1 | bus MIDI RX into the RX node (small signal: low Vf, low leakage) |
| 1k 0805 | 2 | in series with the audio outputs (mispatch and load protection) |
| 100k 0805 | 4 | PCM5102 FLT/DEMP/XSMT/FMT to the module's own rails |
| 100 nF 0805 | 1 | on RUN, at the module pin |
| Shrouded header 2x3 | 1 | bus 1: power and MIDI |
| Header 3-pin | 2 | bus 2: audio; UART0 debug (footprint only) |
| 10k 0805 | 9 | encoder and switch pull-ups |
| 10 nF 0805 | 6 | **buy, leave unpopulated** |
| 100 nF 0805 | 1 | MIDI IN sleeve RF ground, **leave unpopulated** |
| M2 standoff 3.5 mm + screws | 4 | display |
| USB panel socket with lead | 0–1 | optional, and the 10 HP panel has no cutout for it; type follows the module — micro-USB on a Pico 2, USB-C on the Waveshare |

## Checked against the datasheets

- **The boards are drawn for a Raspberry Pi Pico 2**, the module most of the
  instruments in this collection run on. A **Waveshare RP2350-Plus** drops into
  the same sockets when 16 MB of flash is wanted — same 21 x 51 mm outline, same
  40 pins. Which one goes in is a firmware build setting, not a board question;
  see the flash-size note in the [top-level README](../README.md). The one place
  the difference does reach the board is BOOT, below.
- **Everything the board assumes about the module is checked against
  [the Pico 2 datasheet](https://datasheets.raspberrypi.com/pico/pico-2-datasheet.pdf)**,
  not against a footprint that happened to be to hand:

  | | board | datasheet |
  |---|---|---|
  | outline | 21.00 x 51.00 mm | 51 x 21 mm, 1 mm thick |
  | pin pitch | 2.54 mm | 2.54 mm |
  | pin 1 to pin 20 | 48.26 mm | 48.26 mm |
  | row spacing | 17.78 mm | 17.78 mm |
  | pin 1 from the top edge | 1.37 mm | (51 − 48.26)/2 |
  | hole per pin | 1.00 mm | 1 mm |

  Also from the drawing and not used here: four Ø2.1 mm mounting holes, 2 mm in
  from each end and 11.4 mm apart — the module hangs in its sockets, so they stay
  empty.
- **The pin map matches the firmware**, checked pad by pad against
  `core/include/project_config.h`: MIDI on GP4/GP5 → pins 6/7, display on GP2/GP3
  → pins 4/5, I2S on GP26/27/28 → pins 31/32/34, the three encoders on
  GP6-GP8/GP10-GP15, stdio on GP0/GP1 → pins 1/2.
  **This map assumes a Pico-format RP2350A board.** The Waveshare
  RP2350B-Plus-W keeps every one of these positions *except* pins 31/32/34,
  which carry GP40/41/42 there (the RP2350B's ADC0-2 take the Pico's ADC
  positions; GP26-28 are only on the pads underneath). A firmware built for a
  Pico drives GP26-28 into thin air on that board -- display, MIDI and
  encoders work, only the sound is missing. Build it with
  `-DPICOFACE_BOARD=rp2350b_plus_w` instead; see the top-level README. Ground lands on 3, 8, 13, 18,
  23, 28 and 38, and AGND on 33 — which the datasheet allows to be tied to
  digital ground when the ADC is not used, and it is not.
- **RUN is on pin 30** of the Pico format, so the RUN switch works.
- **VSYS is pin 39**, which is where the bus Schottky goes.
- **BOOT is a test pad on the underside**, under the BOOT button (the USB_N /
  USB_P pads sit under the USB connector, the three SWD pads at the far end).
  That pad sits on the button side of the 1 k that separates it from QSPI_SS_N,
  so the BOOT switch goes straight from the pad to ground — no extra resistor. A second button there makes the module
  unbrickable: a firmware too broken to reach its own interface is still
  recoverable without taking it apart.

  BOOT is the only signal on either board that does not end on a connector pin,
  which is why it gets two terminals rather than one:

  **TP2** is a spring-pin landing pad at **25.00 / 15.13**, directly under the
  module's BOOT pad, so the contact is made by seating the module and the module
  stays a plug-in part. That matters: the sockets are in the BOM specifically to
  keep it replaceable, and a soldered wire would tether it. The pin has to span
  **11.04 mm** — socket body 8.5 plus header plastic 2.54, both read out of their
  own STEP models — so roughly 12 mm free length compressing to 11. A crown or
  serrated tip, not a spear: the module's pad is flat and unperforated. It is
  **1.5 x 1.5 mm** though, which is a kinder target than it first looked, and
  leaves room for the tilt a 11 mm free-standing pin will have.

  **Where the position comes from.** Figure 5 of the Pico 2 datasheet, the SMT
  footprint, which gives every test-point centre in a frame whose origin is the
  board's bottom-left corner. The board is 21 x 51 mm there, and the USB shell
  pads at x 7.775 and 13.225 fix the centreline at 10.5. There are **seven** test
  points, not six, and the drawing labels none of them — it only gives
  coordinates, so which one is TP6 has to be reasoned out:

  | coordinate | mm from the USB end | what it must be |
  |---|---|---|
  | (9.5, 49.8), (11.5, 49.8), (10.5, 46.5) | 1.2 / 1.2 / 4.5 | TP1–TP3, the USB group, clustered at the connector |
  | (8, 43) | 8.0 | TP5, GPIO25/LED — the LED sits 7.4 mm from that end |
  | (8, 40.5) | 10.5 | TP4, GPIO23/SMPS PS |
  | **(8, 38)** | **13.0** | **TP6, BOOTSEL — the button sits 13.2 mm from that end** |
  | (11.5, 30.5) | 20.5 | TP7, 1V1, over by the chip |

  The LED and the BOOTSEL button are visible on any photo of the board, and
  measuring both against the three candidates leaves only one reading. The frame
  itself is confirmed independently: it puts pin 1's centre 1.37 mm from the top
  edge, which is exactly what KiCad's `RaspberryPi_Pico_Common_THT` footprint
  uses.

  Which side of the centreline a drawing means is the one thing it cannot say,
  since it does not state the viewing face — **checked on the part, the pad is
  nearer the GP0 row**, and that is the side the board carries. Against the
  module's own features TP6 sits **6.39 mm inwards from the GP0 pin row** and
  **11.63 mm from pin 1 along it**, which is the form to check with callipers.

  **The Waveshare RP2350-Plus is a different PCB**, so its BOOT pad is somewhere
  else and the spring pin will land on bare laminate. That build uses TP1 and a
  wire — which is exactly why TP1 stayed. Nothing needs changing on the board to
  switch between them; you fit either the pin or the wire.

  **TP1 stays** as the fallback, out at the board edge where a soldering iron
  reaches, for the case where the pad turns out to be somewhere else entirely.
  Then it is the short-wire build after all, and nothing has been lost.
- **RUN has only the RP2350's internal ~50k pull-up** (no external one on the
  module), and here it travels over two headers to the tact switch on the front
  board. 100 nF at the module pin (C9) so a touch or a spike does not reset a
  running instrument.
- **GP29 is not brought out**, which independently confirms that `PIN_POT_1` in
  `core/include/project_config.h` is a leftover rather than a connection.
- The pin map fits this board: MIDI on GP4/GP5 lands on **UART1**, which is what
  `midi_serial.cpp` uses, and the display on GP2/GP3 lands on **I2C1**, which is
  what `pico_hw.cpp` initialises.
- The **PCM5102 module takes 3.3–5 V** (two on-board LDOs) and brings its analog
  outputs out on a header row, so the audio bus taps there rather than at its
  own jack. The small purple GY-PCM5102 has a 6-pin digital row (SCK BCK DIN
  LCK GND VIN) and a 9-pin row on the long edge (FLT DEMP XSMT FMT A3V3 AGND
  ROUT AGND LROUT); the schematic sockets both, ties SCK to ground and leaves
  the four format pins to the module's own solder bridges (1=L 2=L 3=H 4=L for
  I2S) — plus 100k pulls to the module's own rails, so a replacement module
  that arrives unbridged still plays. Output is 2.1 Vrms behind 470R — about
  4.5 dB below the 10 Vpp a Eurorack module would normally put out, which is
  why no output stage is planned. The board adds 1k in series (R15/R16): a
  ±12 V Eurorack output patched into ours by mistake is then limited to
  ~8 mA into the DAC's clamps, and a half-inserted plug does not drop the load
  below the PCM5102's 1 kΩ minimum. Into a 100 kΩ input it costs nothing.
- **MIDI at 3.3 V.** In: 220R, reverse 1N4148, H11L1 from 3V3 with 4k7
  pull-up, sleeve left open (CA-033: no DC path to ground at the receiver; a
  100 nF footprint to ground is the RF option the spec allows). The pull-up is
  4k7 rather than the usual few hundred ohms because the bus MIDI RX joins the
  same node through a diode: every module then loads the hub's driver with
  only ~0.6 mA, ten of them with ~6 mA, and the low level at the module stays
  around 0.5 V. The firmware calls `gpio_disable_pulls(PIN_MIDI_RX)` — the
  pad's default pull-down would otherwise divide that pull-up. Out: 33R from
  3V3 to pin 4, 33R from TX to pin 5, sleeve grounded. CA-033's pair is
  33R/10R; 33/33 gives about 4.1 mA worst case into a standard receiver, the
  same class as the 47/47 the Teensy design ships with. The firmware raises
  GP4's drive strength to 12 mA — the default 4 mA is below the loop current.
  Both settings are made in `MIDISerial::init()`; neither is visible from the
  schematic, which is why they are written down on both sides.

## The main board layout

| front | back |
|---|---|
|  |  |

[MainBoard/](MainBoard/) is a second KiCad project, because KiCad wants one
board per project. Its root sheet is a wrapper that pulls in
`../PicoVintageSynthCollection/main_board.kicad_sch` — there is one copy of the
schematic, not two. Every symbol carries a second instance path, which is what
lets one sheet belong to two projects without re-annotating anything. The 19
board-to-board signals end on global labels there, because they leave the board
through J1 / J2.

45 x 80 mm, two layers, 0.2 mm signal tracks (0.3 mm for 3V3 / VSYS / bus 5V),
0.2 mm clearance, 0.6/0.3 mm vias. 630 track segments, 1414 mm of copper, 93
vias — of which about a third are ground stitching. Ground is a pour on both
sides rather than routed.

**Everything sits on the back except J1 / J2 and the eight 0805 parts.** That is
the decision the layout turned on: with the module on the front it would
stand 13.5 mm into the gap between the boards and J1 / J2 would need long-pin
headers, which are a part you have to go looking for. On the back, nothing
between the boards is taller than a 0805, and ordinary headers reach. It also
puts USB, the bus connectors and the module's own BOOT/RESET buttons on the side
you can reach with the module in a case.

- **A1** sits at the top with its USB socket at the board's top edge, so a plug
  can come in from above without dismantling anything. A Pico 2 has **micro-USB**
  (the Waveshare board has USB-C), overhanging its own top edge by 1.3 mm typ.
  The module's edge is 2.13 mm inside the carrier board's, so the socket face
  ends up 0.83 mm *behind* the board edge — which sounds like it would foul a
  plug and does not, because the module stands 11 mm off the back on its sockets
  and the plug arrives in free air well above the board plane. Worth writing down
  so nobody 'fixes' it later.
- **TP2, the BOOT spring-pin pad, cost two reroutes.** It lands where UART0_RX
  used to run, so that net was laid again; the first attempt then took the
  corridor past C9 and pinched the ground pour into an 8.4 mm² island — with
  C9's own ground pad inside it, which would have left the RUN capacitor with no
  return path. The island was too narrow for a stitching via (widest point
  0.468 mm, a 0.6 mm via needs 0.50), so the fix is upstream: that corridor is a
  router keep-out now and UART0_RX goes round. Worth knowing because the same
  trap is waiting for the next track laid through there. BOOT ends up 72.2 mm
  long over two vias, which is long for a node that sits 1k from the flash chip
  select — harmless, because it is only sampled at reset, but it is the reason
  to keep the wire short if the fallback build happens instead.
- **The PCM5102 module** is at the bottom, on the socket offsets taken from the
  STEP model and cross-checked against a KiCad footprint — see
  [PCM5102_module_geometry.md](PCM5102_module_geometry.md). Its own 3.5 mm jack
  (unused) hangs about 11 mm past the bottom edge, which is drawn on
  User.Comments as a reminder.
- **The MIDI section** is down the right-hand strip beside the module, next to
  GP4/GP5 where its signals land.
- **A1's courtyard was clipped** to its own outline plus 0.25 mm. The library
  footprint reserves room for a connector overhang that here points off the
  board. Running "Update Footprints from Library" would put it back and J5 would
  then report a courtyard overlap.

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
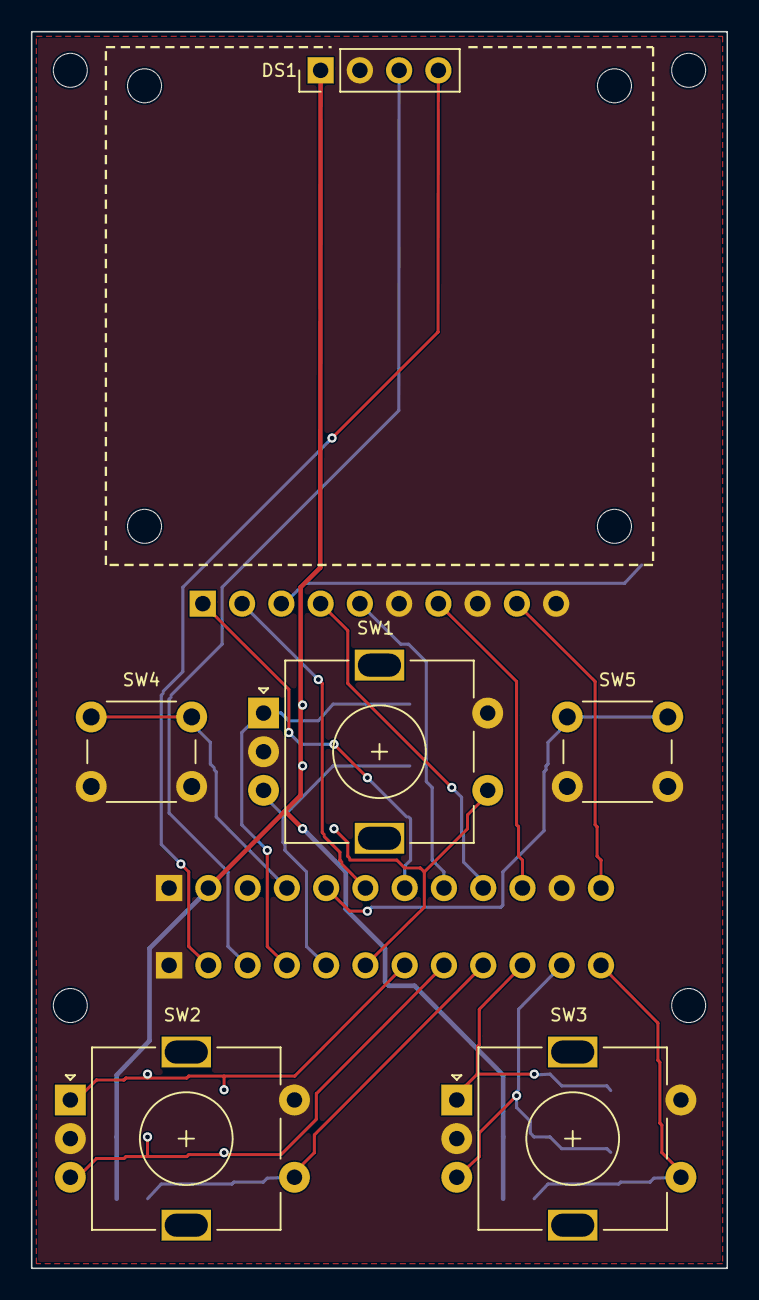
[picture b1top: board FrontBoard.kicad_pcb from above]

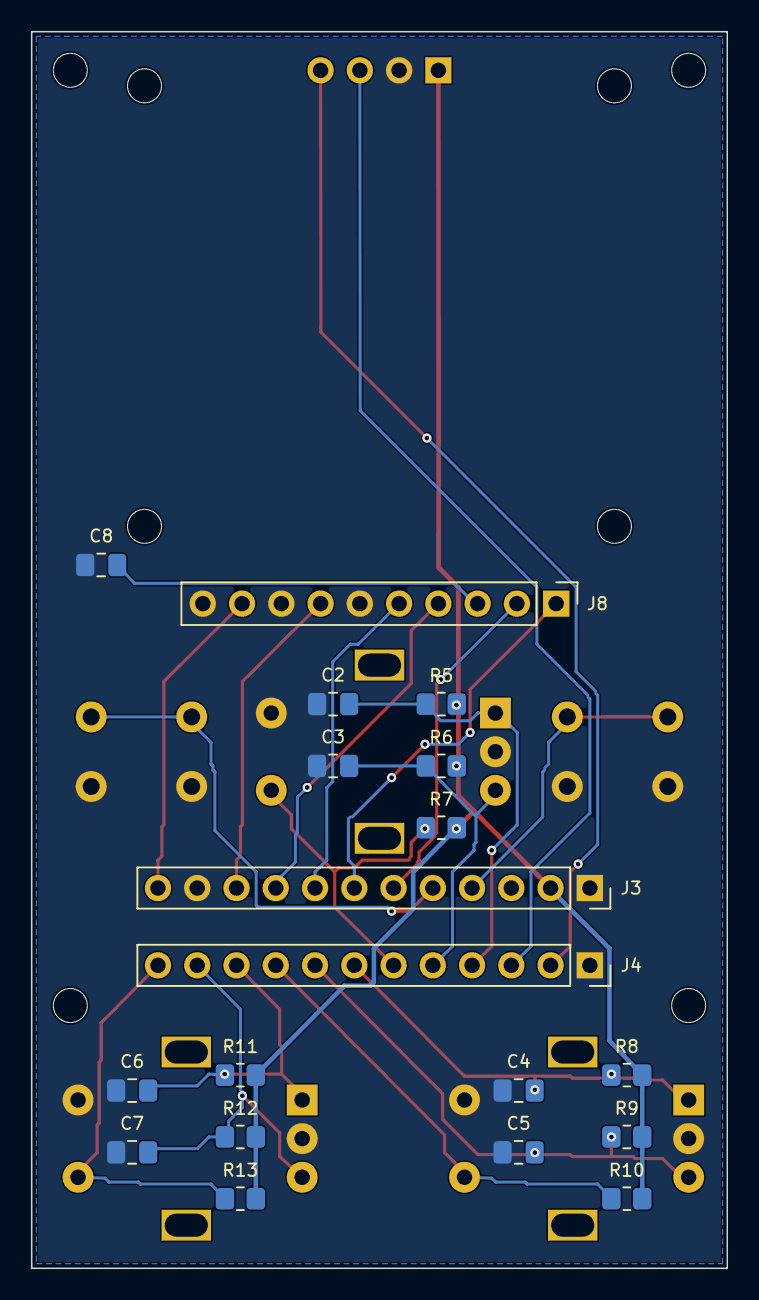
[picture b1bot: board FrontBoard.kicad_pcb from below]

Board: 2 copper layers, 45.0 x 80.0 mm, 33 parts (23 on the bottom side), 22 nets.

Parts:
C2, C3, C4, C5, C6, C7: 10nF; C_0805_2012Metric_Pad1.18x1.45mm_HandSolder
C8: 100nF; C_0805_2012Metric_Pad1.18x1.45mm_HandSolder
DS1: OLED 1.3" SH1106 I2C; PinHeader_1x04_P2.54mm_Vertical
H1, H2, H3, H4: M2 display standoff; MountingHole_2.2mm_M2
H9, H10, H11, H12: M2 board standoff; MountingHole_2.2mm_M2
J3, J4: from main board; PinSocket_1x12_P2.54mm_Vertical
J8: panel jacks; PinHeader_1x10_P2.54mm_Vertical
R5, R6, R7, R8, R9, R10, R11, R12, R13: 10k; R_0805_2012Metric_Pad1.20x1.40mm_HandSolder
SW1: EC11 SEL; RotaryEncoder_Alps_EC11E-Switch_Vertical_H20mm
SW2: EC11 A; RotaryEncoder_Alps_EC11E-Switch_Vertical_H20mm
SW3: EC11 B; RotaryEncoder_Alps_EC11E-Switch_Vertical_H20mm
SW4: RUN; SW_PUSH_6mm
SW5: BOOT; SW_PUSH_6mm

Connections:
+3V3: DS1.1, J3.2, R5.1, R6.1, R7.1, R8.1, R9.1, R10.1, R11.1, R12.1, R13.1
AUDIO_L: J3.10, J8.7
AUDIO_R: J3.12, J8.9
BOOT: J3.5, SW5.1
GND: C2.2, C3.2, C4.2, C5.2, C6.2, C7.2, C8.2, DS1.2, J3.1, J3.11, J4.1, J8.6, J8.8, J8.10, SW1.C, SW1.S2, SW2.C, SW2.S2, SW3.C, SW3.S2, SW4.2, SW5.2
MIDI_IN_4: J3.6, J8.2
MIDI_IN_5: J3.7, J8.1
MIDI_IN_S: C8.1, J8.3
MIDI_OUT_4: J3.8, J8.5
MIDI_OUT_5: J3.9, J8.4
PA_CLK: C4.1, J4.7, R8.2, SW2.A
PA_DT: C5.1, J4.8, R9.2, SW2.B
PA_SW: J4.9, R10.2, SW2.S1
PB_CLK: C6.1, J4.10, R11.2, SW3.A
PB_DT: C7.1, J4.11, R12.2, SW3.B
PB_SW: J4.12, R13.2, SW3.S1
RUN: J3.4, SW4.1
SCL: DS1.3, J4.3
SDA: DS1.4, J4.2
SEL_CLK: C2.1, J4.4, R5.2, SW1.A
SEL_DT: C3.1, J4.5, R6.2, SW1.B
SEL_SW: J4.6, R7.2, SW1.S1

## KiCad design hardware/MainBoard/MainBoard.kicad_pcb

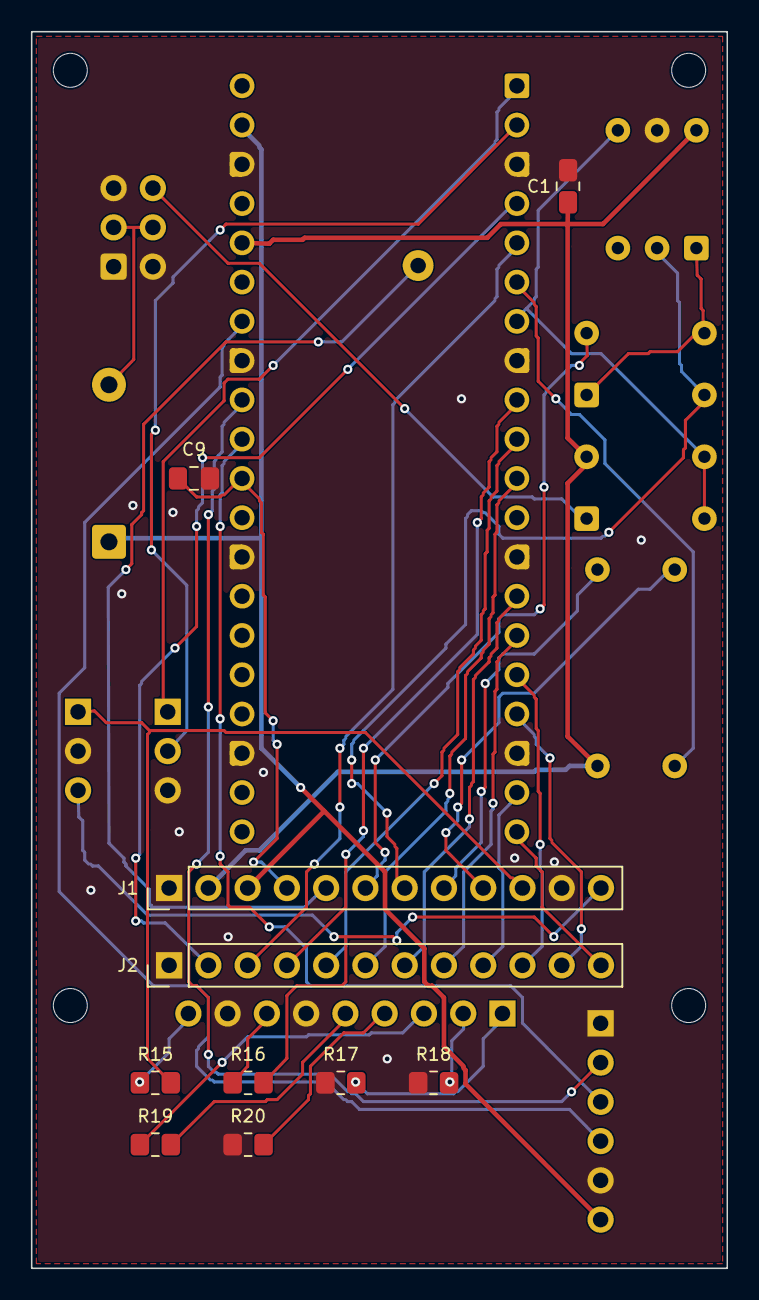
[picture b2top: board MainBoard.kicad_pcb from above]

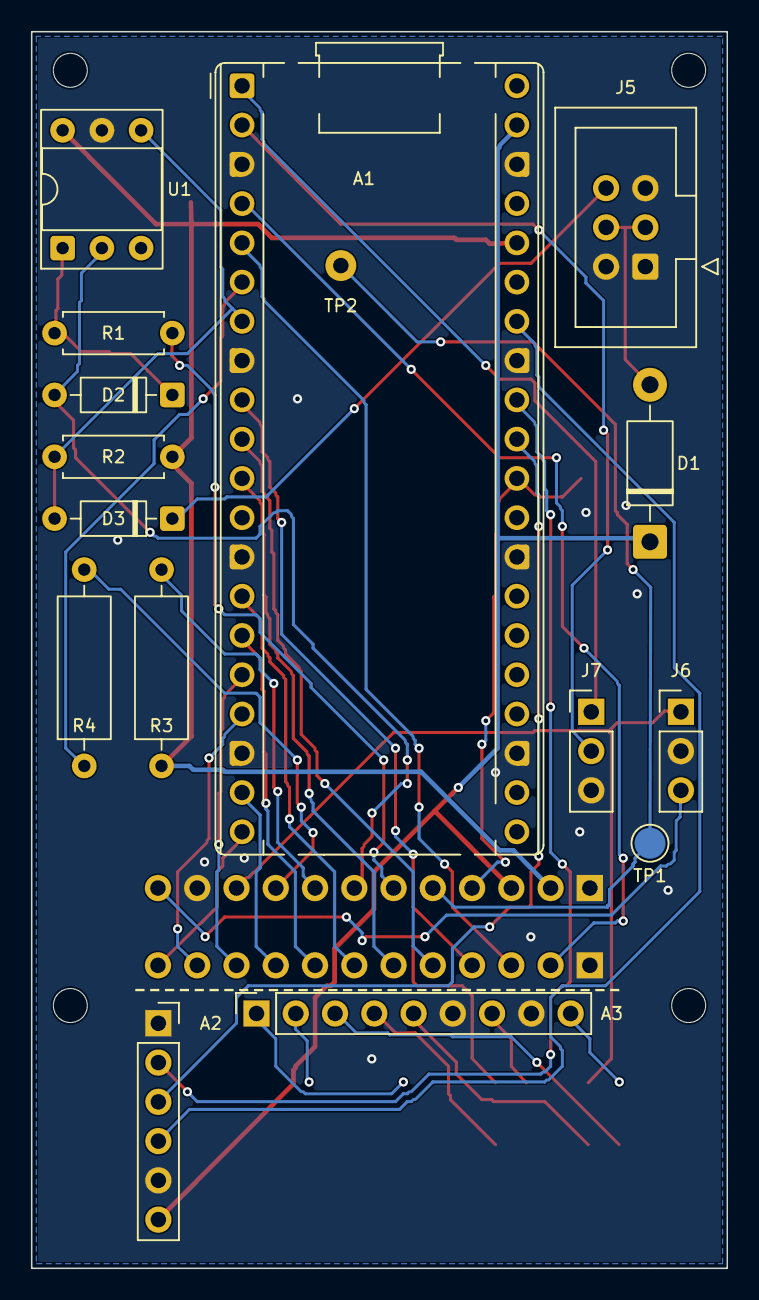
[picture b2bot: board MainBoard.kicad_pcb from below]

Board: 2 copper layers, 45.0 x 80.0 mm, 30 parts (16 on the bottom side), 39 nets.

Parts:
A1: Waveshare RP2350-Plus (16 MB); RaspberryPi_Pico_Common_THT
A2: GY-PCM5102 (digital row); PinSocket_1x06_P2.54mm_Vertical
A3: GY-PCM5102 (analog row); PinSocket_1x09_P2.54mm_Vertical
C1, C9: 100nF; C_0805_2012Metric_Pad1.18x1.45mm_HandSolder
D1: 1N5817; D_DO-41_SOD81_P10.16mm_Horizontal
D2: 1N4148; D_DO-35_SOD27_P7.62mm_Horizontal
D3: BAT85; D_DO-35_SOD27_P7.62mm_Horizontal
H5, H6, H7, H8: M2 board standoff; MountingHole_2.2mm_M2
J1, J2: to front board; PinHeader_1x12_P2.54mm_Vertical
J5: Bus 1 power/MIDI; IDC-Header_2x03_P2.54mm_Vertical
J6: Bus 2 audio; PinHeader_1x03_P2.54mm_Vertical
J7: DEBUG UART0; PinHeader_1x03_P2.54mm_Vertical
R1: 220R; R_Axial_DIN0207_L6.3mm_D2.5mm_P7.62mm_Horizontal
R2: 4k7; R_Axial_DIN0207_L6.3mm_D2.5mm_P7.62mm_Horizontal
R3, R4: 33R 0.5W; R_Axial_DIN0309_L9.0mm_D3.2mm_P12.70mm_Horizontal
R15, R16: 1k; R_0805_2012Metric_Pad1.20x1.40mm_HandSolder
R17, R18, R19, R20: 100k; R_0805_2012Metric_Pad1.20x1.40mm_HandSolder
TP1: BOOT; TestPoint_Pad_D2.0mm
TP2: BOOT pogo; TestPoint_THTPad_D2.0mm_Drill1.0mm
U1: H11L1; DIP-6_W7.62mm_Socket

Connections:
+3V3: A1.36, C1.1, J1.2, R2.1, R3.1, U1.6
/Main board/A3V3: A3.5, R19.2
/Main board/BUS_5V: D1.2, J5.3, J5.4
/Main board/BUS_MIDI_RX: D3.1, J5.6
/Main board/I2S_BCK: A1.32, A2.2
/Main board/I2S_DIN: A1.31, A2.3
/Main board/I2S_LRCK: A1.34, A2.4
/Main board/MIDI_RX: A1.7, D3.2, R2.2, U1.4
/Main board/MIDI_TX: A1.6, R4.1
/Main board/UART0_RX: A1.2, J7.2
/Main board/UART0_TX: A1.1, J7.1
AUDIO_L: J1.10, J6.1, R15.2
AUDIO_R: J1.12, J6.3, R16.2
BOOT: J1.5, TP1.1, TP2.1
GND: A1.3, A1.8, A1.13, A1.18, A1.23, A1.28, A1.33, A1.38, A2.1, A2.5, A3.6, A3.8, C1.2, C9.2, J1.1, J1.11, J2.1, J5.1, J5.2, J5.5, J6.2, J7.3, R17.1, R18.1, R20.1, U1.5
MIDI_IN_4: J1.6, R1.1
MIDI_IN_5: D2.2, J1.7, U1.2
MIDI_OUT_4: J1.8, R3.2
MIDI_OUT_5: J1.9, R4.2
unnamed: A3.2, R18.2
unnamed: A3.1, R17.2
unnamed: A3.4, R20.2
unnamed: A3.9, R15.1
unnamed: A3.7, R16.1
unnamed: A3.3, R19.1
unnamed: D2.1, R1.2, U1.1
PA_CLK: A1.14, J2.7
PA_DT: A1.15, J2.8
PA_SW: A1.19, J2.9
PB_CLK: A1.16, J2.10
PB_DT: A1.17, J2.11
PB_SW: A1.20, J2.12
RUN: A1.30, C9.1, J1.4
SCL: A1.5, J2.3
SDA: A1.4, J2.2
SEL_CLK: A1.9, J2.4
SEL_DT: A1.10, J2.5
SEL_SW: A1.11, J2.6
VSYS: A1.39, A2.6, D1.1, J1.3

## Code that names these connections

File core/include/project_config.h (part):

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
// DIN MIDI on uart1, behind the opto-coupler on the board. uart0 (GPIO 0/1)
// stays reserved for stdio, so the two never collide.
#define PIN_MIDI_RX 5
#define PIN_MIDI_TX 4

// Pimoroni Pico Audio
//#define PIN_I2S_DOUT  9
//#define PIN_I2S_BCK   10
//#define PIN_I2S_WS    11

// Waveshare Pico Audio
#define PIN_I2S_DOUT  26
#define PIN_I2S_BCK   27
#define PIN_I2S_WS    28

#define  PIN_LED	  25
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// pairing works.

// Selector encoder
#define PIN_SEL_CLK   7
#define PIN_SEL_DT    6
#define PIN_SEL_SW    8

// Param A encoder
#define PIN_PA_CLK    11
#define PIN_PA_DT     10
#define PIN_PA_SW     14   // optional switch

// Param B encoder
#define PIN_PB_CLK    13
#define PIN_PB_DT     12
#define PIN_PB_SW     15   // optional switch

// QMI M0_TIMING values. Bit layout (see hardware/regs/qmi.h):
//   CLKDIV  [7:0]   flash clock = clk_sys / CLKDIV
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

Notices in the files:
core/include/project_config.h:
SPDX-License-Identifier: GPL-3.0-or-later
SPDX-FileCopyrightText: 2026 Michi71
